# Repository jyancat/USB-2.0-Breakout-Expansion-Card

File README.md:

# USB 2.0 Breakout Expansion Card
 This is a repository for all the design files for the USB 2.0 Breakout Expansion Card. UNTESTED

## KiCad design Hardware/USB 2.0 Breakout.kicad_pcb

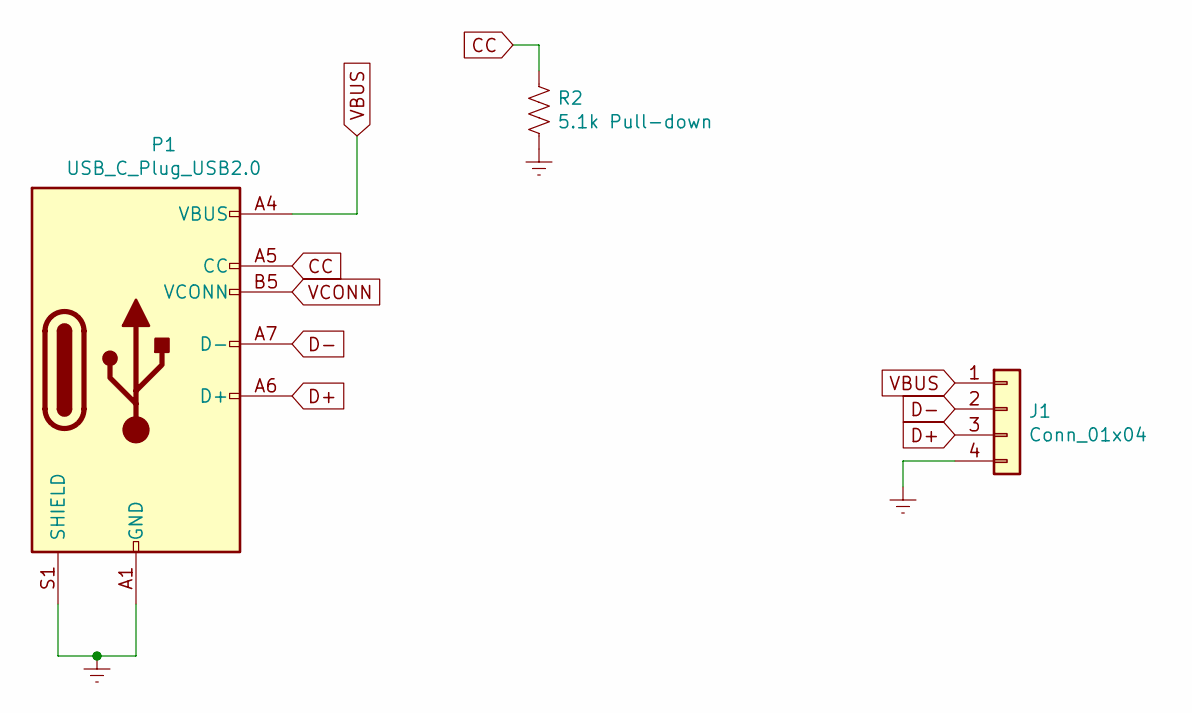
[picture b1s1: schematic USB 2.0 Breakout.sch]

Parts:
J1: Conn_01x04; PinHeader_1x04_P2.54mm_Horizontal
P1: USB_C_Plug_USB2.0; USB_C_Plug_Molex_105444
R2: 5.1k Pull-down; R_0805_2012Metric

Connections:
CC: P1.A5 (CC), R2.1
D+: J1.3, P1.A6 (D+)
D-: J1.2, P1.A7 (D-)
Earth: J1.4, P1.A1 (GND), P1.A12 (GND), P1.B1 (GND), P1.B12 (GND), P1.S1 (SHIELD), R2.2
VBUS: J1.1, P1.A4 (VBUS), P1.A9 (VBUS), P1.B4 (VBUS), P1.B9 (VBUS)
VCONN: P1.B5 (VCONN)

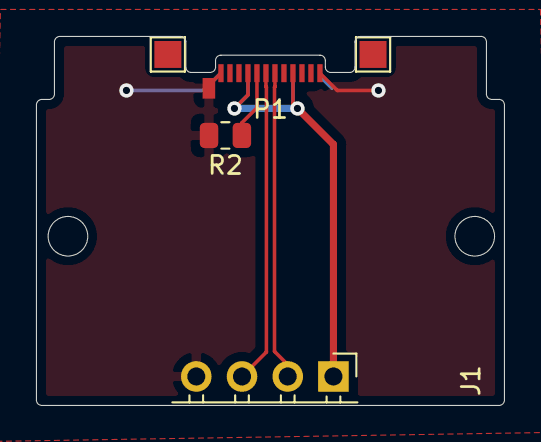
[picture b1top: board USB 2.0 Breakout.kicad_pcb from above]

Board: 2 copper layers, 26.0 x 20.5 mm, 7 parts (0 on the bottom side), 5 nets.

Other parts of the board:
H1, H2: MountingHole; MountingHole_2.2mm_M2
TP1, TP3: TestPoint; TestPoint_Pad_1.5x1.5mm

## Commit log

2022-05-04 Added new files.
2022-05-28 Updated files
